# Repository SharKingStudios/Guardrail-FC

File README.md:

# Guardrail FC - A Flight Assist that helps you not crash!

### With a side of data logging and autopilot.

---

## Renders
*visuals because everyone loves eye candy.*

---

## BOM
All the sensing and thinky bits live **[here](/BOM.csv)**.

**Main characters:**
 - **Microcontroller:** RP2040
 - **Storage:** W25Q16JVUXIQ 16Mbit SPI flash
 - **Sensors:**
   - ICM-42688P-HXY 6-axis IMU
   - SAM-M8Q-0 GNSS module
   - SPA06-003 pressure sensor
 - **Misc:** Boot circuitry, pull-ups, decoupling, and other necessary magic

(See `BOM.csv` for full part values, footprints, and sourcing.)

---

## What is this?

The **Guardrail FC** is a **Flight Controller** built around a RP2040 microcontroller and a handful of sensors, designed to help you not crash your RC planes and drones!

It does this by sitting in the middle of the data signals between the RC reciever and the plane's control surfaces / throttle. The board will use the pilot's input to steer the plane, but will lock the plane to certain bank angles in order to prevent the plane from flipping upside down and crashing. The board also logs all the sensor data and pilot inputs to its onboard flash, which can be retrieved after the flight to analyze flight characteristics afterwards.

---

## How It Works

On startup, the board will continuously read the IMU, GNSS, and pressure sensors to get an idea of the plane's orientation, position, and altitude. From these readings, the board calculates what angles the servos need to be at to get to a certain desired angle using a PID loop.

The board will then read the pilot's input from the RC receiver, and use that to control the desired angle for the plane.

At a high level:
1. Read sensors to get current orientation, position, and altitude.
2. Read pilot input to get desired angle.
3. Use PID loop to calculate servo angles needed to achieve desired angle.
4. Output servo angles to control surfaces and throttle.

---

## Features

### Flight Assist
The main feature of the Guardrail FC is its flight assist capabilities. By using the IMU data, the board can determine the plane's current orientation and adjust the control surfaces to keep the plane within a certain bank angle, preventing it from flipping upside down and crashing.

### Data Logging
The board logs all sensor data and pilot inputs to its onboard flash memory. This allows you to analyze flight characteristics after the flight.

### Autopilot
In addition to flight assist, the firmware includes a guarded automatic-throttle mode that uses pressure altitude, vertical speed, aircraft attitude, and optional GNSS ground speed. Waypoint navigation remains future work.

---

## Firmware

The firmware lives in **[`Firmware/`](/Firmware/)** and is written in Python using MicroPython. Interrupt-driven input capture keeps all ten receiver channels live while the controller reads sensors and logs the flight.

See the [`Firmware/README.md`](/Firmware/README.md) for more details on how to set up the firmware and tune the board for your specific plane.

---

### Why?

Because crashing is bad, and this board helps you not crash! I've had an interest in RC planes and drones for a while, and by making this board, I can run whatever kind of firmware I want to create interesting flight characteristics. One of my friends recently created and crasshed their custom built plane, and I wanted to make something that might have been able to save it!

---

## Contributing

This is a personal project, but if you have any ideas or suggestions, feel free to open an issue or submit a pull request! I'm always open to feedback and improvements.

## Disclaimer

This project is still in development, and I have yet to test it in flight. Remember to test in a safe environment before flying with hardware from a random internet person! I am not responsible for any crashes or damage caused by this board. Use at your own risk!

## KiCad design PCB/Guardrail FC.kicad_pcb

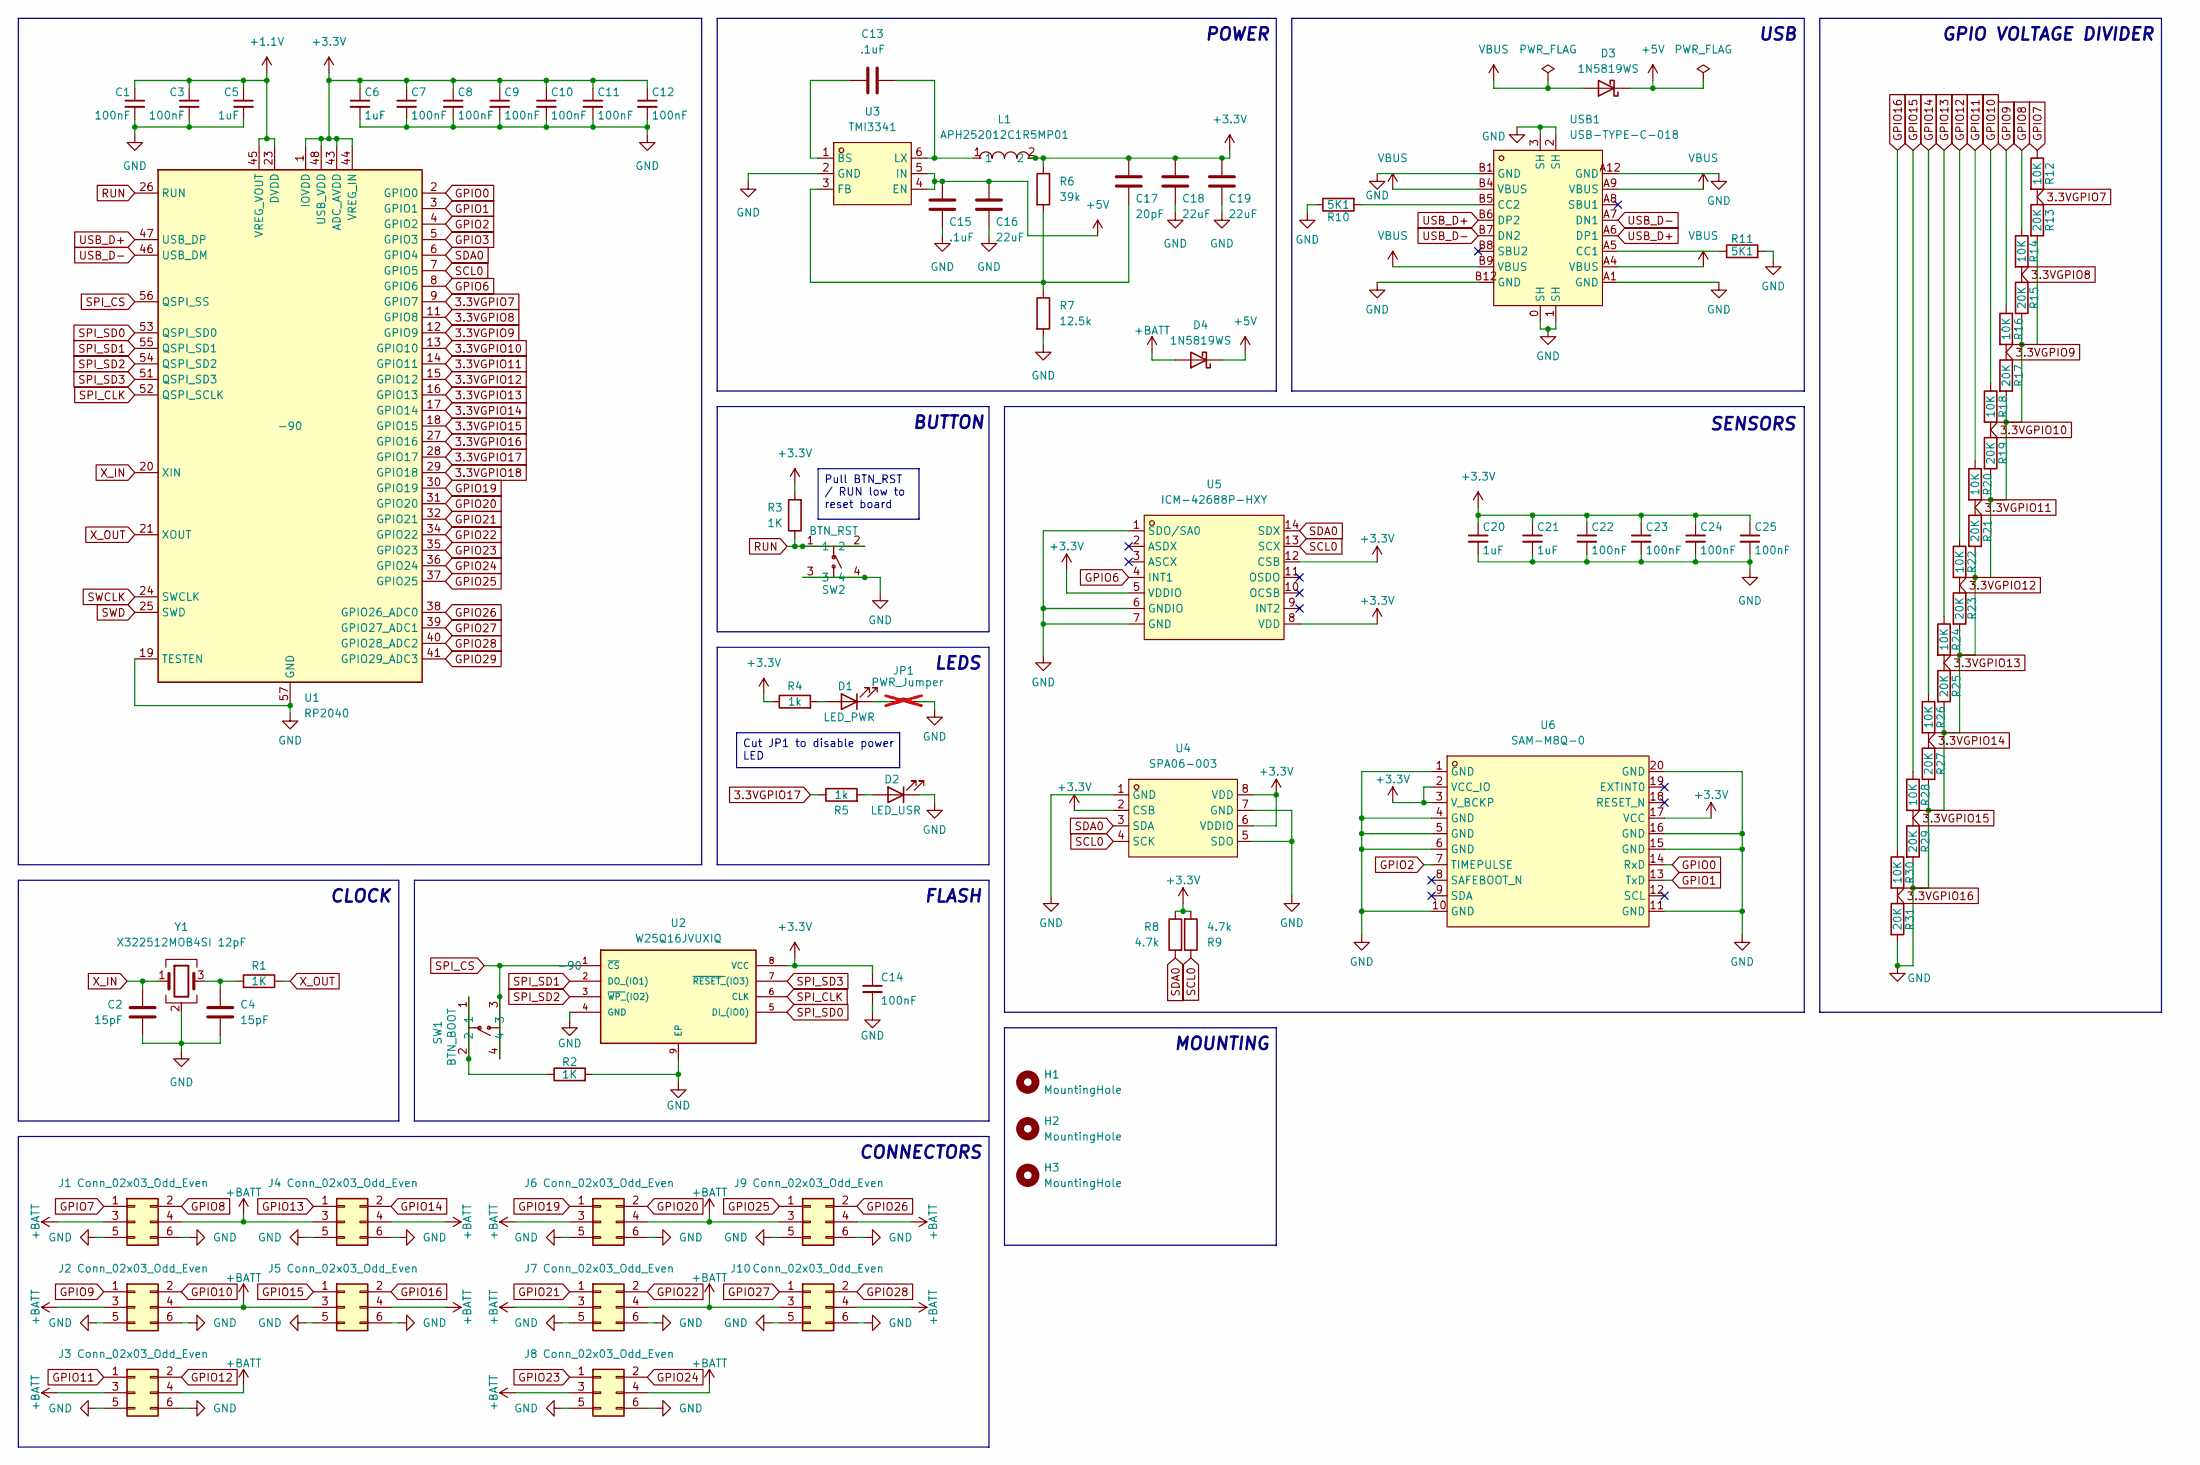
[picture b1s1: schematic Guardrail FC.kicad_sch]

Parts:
C1, C3, C7, C8, C9, C10, C11, C12, C14, C22, C23, C24, C25: 100nF; C_0603_1608Metric_Pad1.08x0.95mm_HandSolder; LCSC C1525
C2, C4: 15pF; C_0603_1608Metric_Pad1.08x0.95mm_HandSolder; LCSC C1548
C5, C6: 1uF; C_0603_1608Metric_Pad1.08x0.95mm_HandSolder; LCSC C52923
C13, C15: .1uF; C_0603_1608Metric_Pad1.08x0.95mm_HandSolder
C16, C18, C19: 22uF; C_0603_1608Metric_Pad1.08x0.95mm_HandSolder
C17: 20pF; C_0603_1608Metric_Pad1.08x0.95mm_HandSolder
C20, C21: 1uF; C_0603_1608Metric_Pad1.08x0.95mm_HandSolder; LCSC C1525
D1: LED_PWR; LED_0603_1608Metric; LCSC C2286
D2: LED_USR; LED_0603_1608Metric; LCSC C2286
D3, D4: 1N5819WS; D_SOD-323; LCSC C191023
H1, H2, H3: MountingHole; MountingHole_2.2mm_M2_Pad_Via
J1, J2, J3, J4, J5, J6, J7, J8, J9, J10: Conn_02x03_Odd_Even; HDR-SMD_6P-P2.54-V
JP1: PWR_Jumper; SolderJumper-2_P1.3mm_Bridged2Bar_RoundedPad1.0x1.5mm; not fitted
L1: APH252012C1R5MP01; IND-SMD_APH252012C3R3MP01; MPN APH252012C1R5MP01; LCSC Part C42455360
R1, R2, R3: 1K; R_0603_1608Metric_Pad0.98x0.95mm_HandSolder; LCSC C11702
R4, R5: 1k; R_0603_1608Metric_Pad0.98x0.95mm_HandSolder; LCSC C11702
R6: 39k; R_0603_1608Metric_Pad0.98x0.95mm_HandSolder
R7: 12.5k; R_0603_1608Metric_Pad0.98x0.95mm_HandSolder
R8, R9: 4.7k; R_0603_1608Metric_Pad0.98x0.95mm_HandSolder
R10, R11: 5K1; R_0603_1608Metric_Pad0.98x0.95mm_HandSolder; LCSC C25905
R12, R14, R16, R18, R20, R22, R24, R26, R28, R30: 10K; R_0603_1608Metric_Pad0.98x0.95mm_HandSolder; LCSC C11702
R13, R15, R17, R19, R21, R23, R25, R27, R29, R31: 20K; R_0603_1608Metric_Pad0.98x0.95mm_HandSolder; LCSC C11702
SW1: BTN_BOOT; SW-SMD_4P-L5.2-W5.2-P5.80-LS6.4; MPN LXW-52X52X2-SMD; LCSC Part C53447014
SW2: BTN_RST; SW-SMD_4P-L5.2-W5.2-P5.80-LS6.4; MPN LXW-52X52X2-SMD; LCSC Part C53447014
U1: RP2040; QFN-56-1EP_7x7mm_P0.4mm_EP3.2x3.2mm; LCSC C2040
U2: W25Q16JVUXIQ; Winbond_USON-8-1EP_3x2mm_P0.5mm_EP0.2x1.6mm; LCSC C2843335
U3: TMI3341; SOT-23-6_L2.9-W1.6-P0.95-LS2.8-BL; MPN TMI3341; LCSC Part C5182732
U4: SPA06-003; LGA-8_L2.5-W2.0-P0.65_SPA06-003; MPN SPA06-003; LCSC Part C30589048
U5: ICM-42688P-HXY; LGA-14_L3.0-W2.5-P0.50-TL; MPN ICM-42688P-HXY; LCSC Part C46550687
U6: SAM-M8Q-0; LCC-20_L15.5-W15.5-P1.90_SAM-M10Q-00B; MPN SAM-M8Q-0; LCSC Part C5447387
USB1: USB-TYPE-C-018; USB-C_SMD-TYPE-C-31-M-12; MPN USB-TYPE-C-018; LCSC Part C2927038
Y1: X322512MOB4SI 12pF; Crystal_SMD_3225-4Pin_3.2x2.5mm; LCSC C70565

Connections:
3.3VGPIO7: R12.2, R13.1, U1.9 (GPIO7)
3.3VGPIO8: R14.2, R15.1, U1.11 (GPIO8)
3.3VGPIO9: R16.2, R17.1, U1.12 (GPIO9)
3.3VGPIO10: R18.2, R19.1, U1.13 (GPIO10)
3.3VGPIO11: R20.2, R21.1, U1.14 (GPIO11)
3.3VGPIO12: R22.2, R23.1, U1.15 (GPIO12)
3.3VGPIO13: R24.2, R25.1, U1.16 (GPIO13)
3.3VGPIO14: R26.2, R27.1, U1.17 (GPIO14)
3.3VGPIO15: R28.2, R29.1, U1.18 (GPIO15)
3.3VGPIO16: R30.2, R31.1, U1.27 (GPIO16)
3.3VGPIO17: R5.1, U1.28 (GPIO17)
3.3VGPIO18: U1.29 (GPIO18)
+1.1V: C1.1, C3.1, C5.1, U1.23 (DVDD), U1.45 (VREG_VOUT), U1.50 (DVDD)
+3.3V: C6.1, C7.1, C8.1, C9.1, C10.1, C11.1, C12.1, C14.1, C17.2, C18.2, C19.2, C20.1, C21.1, C22.1, C23.1, C24.1, C25.1, L1.2, R3.2, R4.1, R6.1, R8.1, R9.2, U1.1 (IOVDD), U1.10 (IOVDD), U1.22 (IOVDD), U1.33 (IOVDD), U1.42 (IOVDD), U1.43 (ADC_AVDD), U1.44 (VREG_IN), U1.48 (USB_VDD), U1.49 (IOVDD), U2.8 (VCC), U4.2 (CSB), U4.6 (VDDIO), U4.8 (VDD), U5.5 (VDDIO), U5.8 (VDD), U5.12 (CSB), U6.2 (VCC_IO), U6.3 (V_BCKP), U6.17 (VCC)
+5V: C15.2, C16.2, D3.1 (K), D4.1 (K), U3.4 (EN), U3.5 (IN)
+BATT: D4.2 (A), J1.3, J1.4, J2.3, J2.4, J3.3, J3.4, J4.3, J4.4, J5.3, J5.4, J6.3, J6.4, J7.3, J7.4, J8.3, J8.4, J9.3, J9.4, J10.3, J10.4
GND: C1.2, C2.1, C3.2, C4.2, C5.2, C6.2, C7.2, C8.2, C9.2, C10.2, C11.2, C12.2, C14.2, C15.1, C16.1, C18.1, C19.1, C20.2, C21.2, C22.2, C23.2, C24.2, C25.2, D2.1 (K), J1.5, J1.6, J2.5, J2.6, J3.5, J3.6, J4.5, J4.6, J5.5, J5.6, J6.5, J6.6, J7.5, J7.6, J8.5, J8.6, J9.5, J9.6, J10.5, J10.6, JP1.2 (B), R2.2, R7.2, R10.1, R11.2, R13.2, R15.2, R17.2, R19.2, R21.2, R23.2, R25.2, R27.2, R29.2, R31.2, SW2.3, SW2.4, U1.19 (TESTEN), U1.57 (GND), U2.4 (GND), U2.9 (EP), U3.2 (GND), U4.1 (GND), U4.5 (SDO), U4.7 (GND), U5.1 (SDO/SA0), U5.6 (GNDIO), U5.7 (GND), U6.1 (GND), U6.4 (GND), U6.5 (GND), U6.6 (GND), U6.10 (GND), U6.11 (GND), U6.15 (GND), U6.16 (GND), U6.20 (GND), USB1.0 (SH), USB1.1 (SH), USB1.2 (SH), USB1.3 (SH), USB1.A1 (GND), USB1.A12 (GND), USB1.B1 (GND), USB1.B12 (GND), Y1.2 (G), Y1.4 (G)
GPIO0: U1.2 (GPIO0), U6.14 (RxD)
GPIO1: U1.3 (GPIO1), U6.13 (TxD)
GPIO2: U1.4 (GPIO2), U6.7 (TIMEPULSE)
GPIO3: U1.5 (GPIO3)
GPIO6: U1.8 (GPIO6), U5.4 (INT1)
GPIO7: J1.1, R12.1
GPIO8: J1.2, R14.1
GPIO9: J2.1, R16.1
GPIO10: J2.2, R18.1
GPIO11: J3.1, R20.1
GPIO12: J3.2, R22.1
GPIO13: J4.1, R24.1
GPIO14: J4.2, R26.1
GPIO15: J5.1, R28.1
GPIO16: J5.2, R30.1
GPIO19: J6.1, U1.30 (GPIO19)
GPIO20: J6.2, U1.31 (GPIO20)
GPIO21: J7.1, U1.32 (GPIO21)
GPIO22: J7.2, U1.34 (GPIO22)
GPIO23: J8.1, U1.35 (GPIO23)
GPIO24: J8.2, U1.36 (GPIO24)
GPIO25: J9.1, U1.37 (GPIO25)
GPIO26: J9.2, U1.38 (GPIO26_ADC0)
GPIO27: J10.1, U1.39 (GPIO27_ADC1)
GPIO28: J10.2, U1.40 (GPIO28_ADC2)
GPIO29: U1.41 (GPIO29_ADC3)
unnamed: C4.1, R1.2, Y1.3
unnamed: D1.2 (A), R4.2
unnamed: D1.1 (K), JP1.1 (A)
unnamed: D2.2 (A), R5.2
unnamed: R2.1, SW1.1, SW1.2
unnamed: C13.1, U3.1 (BS)
unnamed: C17.1, R6.2, R7.1, U3.3 (FB)
unnamed: C13.2, L1.1, U3.6 (LX)
unnamed: R11.1, USB1.A5 (CC1)
unnamed: R10.2, USB1.B5 (CC2)
RUN: R3.1, SW2.1, SW2.2, U1.26 (RUN)
SCL0: R9.1, U1.7 (GPIO5), U4.4 (SCK), U5.13 (SCX)
SDA0: R8.2, U1.6 (GPIO4), U4.3 (SDA), U5.14 (SDX)
SPI_CLK: U1.52 (QSPI_SCLK), U2.6 (CLK)
SPI_CS: SW1.3, SW1.4, U1.56 (QSPI_SS), U2.1 (~CS)
SPI_SD0: U1.53 (QSPI_SD0), U2.5 (DI_(IO0))
SPI_SD1: U1.55 (QSPI_SD1), U2.2 (DO_(IO1))
SPI_SD2: U1.54 (QSPI_SD2), U2.3 (~WP_(IO2))
SPI_SD3: U1.51 (QSPI_SD3), U2.7 (~RESET_(IO3))
SWCLK: U1.24 (SWCLK)
SWD: U1.25 (SWD)
USB_D+: U1.47 (USB_DP), USB1.A6 (DP1), USB1.B6 (DP2)
USB_D-: U1.46 (USB_DM), USB1.A7 (DN1), USB1.B7 (DN2)
VBUS: D3.2 (A), USB1.A4 (VBUS), USB1.A9 (VBUS), USB1.B4 (VBUS), USB1.B9 (VBUS)
X_IN: C2.2, U1.20 (XIN), Y1.1
X_OUT: R1.1, U1.21 (XOUT)

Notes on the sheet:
BUTTON
MOUNTING
GPIO VOLTAGE DIVIDER
CONNECTORS
USB
CLOCK
POWER
SENSORS
LEDS
FLASH
Cut JP1 to disable power LED
Pull BTN_RST / RUN low to reset board

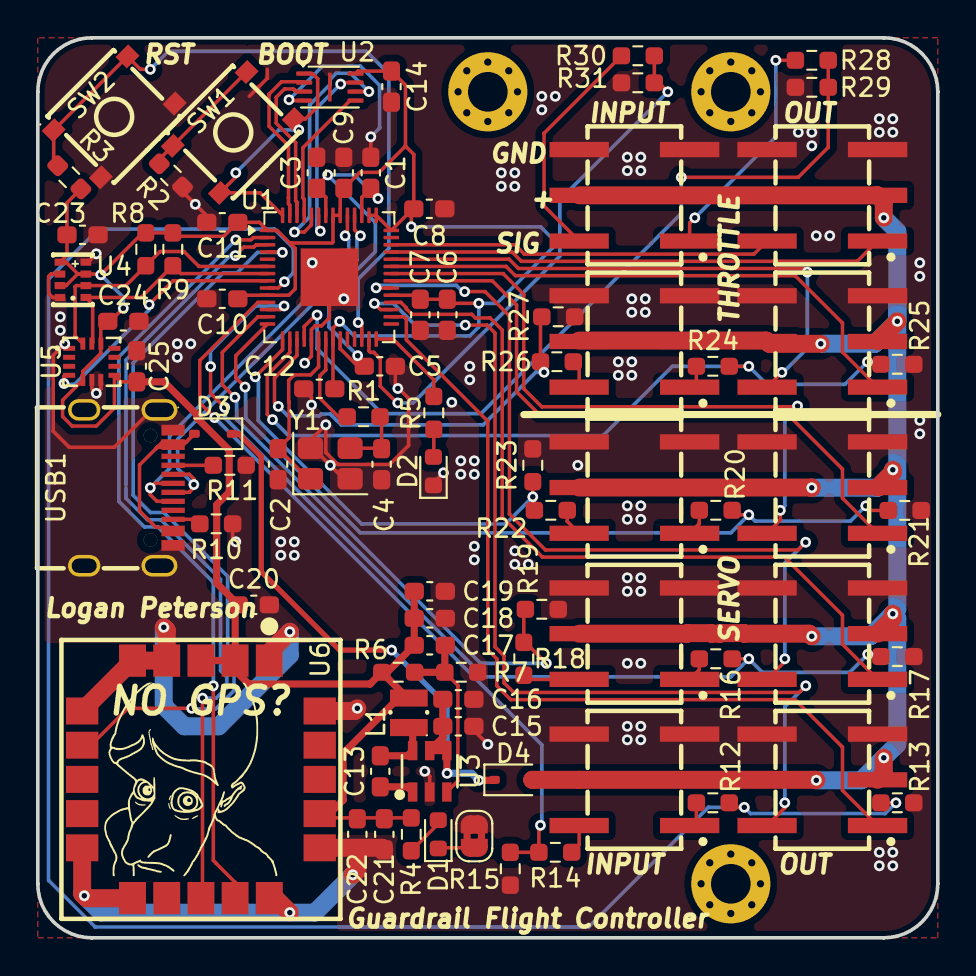
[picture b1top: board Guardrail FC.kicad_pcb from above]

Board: 2 copper layers, 50.0 x 50.0 mm, 86 parts (0 on the bottom side), 64 nets.

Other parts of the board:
NO GPS?: LOGO

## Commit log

2026-06-16 Init
2026-06-19 PCB Done!
2026-06-19 BOM Finished
2026-06-19 Update BOM
2026-06-20 README + Zine + Firmware Done!
